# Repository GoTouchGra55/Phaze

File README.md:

# Phaze
A field-oriented control board designed to be used with a brushless motor.

## Overview
Phaze is my attempt at making a custom FOC driver. It utilizes the CAN protocol for communication between a main board and the driver, but it can also be programmed directly via an STLink-V2 debugger. 

The main goal of this project was to explore the hardware side of field-oriented control, especially the design of a dedicated motor driver and the electronics required to control a bldc motor. I wanted to design my own board and understand how all the different sections work together, rather than relying on any existing motor controllers.

## Design

SEE [SCHEMATICS](KiCAD/Phaze.pdf)

## Build Instructions
1. Order the PCB using the provided [files](KiCAD/production).
2. Solder all SMD components according to the schematic and PCB layout.
3. Inspect all solder joints and check for shorts.
4. Connect the peripherals according to the schematic.
5. Flash the firmware and verify all interfaces.
6. Test the power rails before connecting the motors.

## IMPORTANT
1. Use a 3-4s LiPo battery if you decide to use this board in your project. Discard the battery if it smells "funny".

2. Check for any damage on the pcb as it can be the reason for a catastrophic failure.

## Bill Of Materials
| # | Component / Item | Specifications | Qty. | Price (USD) | Link |
|---:|---|---|---:|---:|---:|
| 1 | SMD Resistor Assortment | 660 pcs, mixed packages and values | 1  | $0 | [Daraz](https://www.daraz.com.np/products/000000pcs-040222-10hm-910k-ohm-5-80llasex-cp0pcs-u003d-4000pcs-i416649373-s1793309546.html?c=&channelLpJumpArgs=&clickTrackInfo=query%253Asmd%252Bresistors%253Bnid%253A416649373%253Bsrc%253ALazadaMainSrp%253Brn%253Aa5197133a3019ce49e53177277acb4a7%253Bregion%253Anp%253Bsku%253A416649373_NP%253Bprice%253A1305%253Bclient%253Adesktop%253Bsupplier_id%253A900273856834%253Bsession_id%253A%253Bbiz_source%253Ahttps%253A%252F%252Fwww.daraz.com.np%252F%253Bslot%253A5%253Butlog_bucket_id%253A470687%253Basc_category_id%253A10000489%253Bitem_id%253A416649373%253Bsku_id%253A1793309546%253Bshop_id%253A191864%253BtemplateInfo%253A&freeshipping=0&fs_ab=1&fuse_fs=&lang=en&location=Overseas&price=1305&priceCompare=skuId%3A1793309546%3Bsource%3Alazada-search-voucher%3Bsn%3Aa5197133a3019ce49e53177277acb4a7%3BoriginPrice%3A130500%3BdisplayPrice%3A130500%3BisGray%3Afalse%3BsinglePromotionId%3A-1%3BsingleToolCode%3AmockedSalePrice%3BvoucherPricePlugin%3A0%3Btimestamp%3A1794537582362&ratingscore=&request_id=a5197133a3019ce49e53177277acb4a7&review=&sale=3&search=1&source=search&spm=a2a0e.searchlist.list.5&stock=1) |
| 2 | SMD Ceramic Capacitor Assortment | 2,500 pcs, 50 values, mixed packages | 1  | $0 | [Daraz](https://www.daraz.com.np/products/2500pcs-50-values-capacitor-smd-0402-0603-0805-smd-ceramic-capacitors-assortment-kit-1p-10uf-1pf-5pf-10pf-100pf-1nf-102-333-474-i1514281975-s12310158935.html?c=&channelLpJumpArgs=&clickTrackInfo=query%253Asmd%252Bcapacitor%252B0402%253Bnid%253A1514281975%253Bsrc%253ALazadaMainSrp%253Brn%253Abb4c895be7dbb09066bdbc9410dfb62b%253Bregion%253Anp%253Bsku%253A1514281975_NP%253Bprice%253A1356%253Bclient%253Adesktop%253Bsupplier_id%253A900279168309%253Bsession_id%253A%253Bbiz_source%253Ah5_external%253Bslot%253A0%253Butlog_bucket_id%253A470687%253Basc_category_id%253A10001489%253Bitem_id%253A1514281975%253Bsku_id%253A12310158935%253Bshop_id%253A198893%253BtemplateInfo%253A&configId=choice_NP_promotion&freeshipping=0&fs_ab=1&fuse_fs=&lang=en&location=Overseas&price=1356&priceCompare=skuId%3A12310158935%3Bsource%3Alazada-search-voucher%3Bsn%3Abb4c895be7dbb09066bdbc9410dfb62b%3BoriginPrice%3A135600%3BdisplayPrice%3A135600%3BisGray%3Afalse%3BsinglePromotionId%3A-1%3BsingleToolCode%3AmockedSalePrice%3BvoucherPricePlugin%3A0%3Btimestamp%3A1794537638805&ratingscore=&request_id=bb4c895be7dbb09066bdbc9410dfb62b&review=&sale=0&search=1&source=search&spm=a211g0.searchlist.list.0&stock=1&upItemIds=1514281975) |
| 3 | JLCPCB PCB Fabrication & Assembly | PCB manufacturing and assembly order | 1 order | $241.02 | [JLCPCB](https://jlcpcb.com)
| | **GRAND TOTAL** | | | **$241.02** | |

## License
### MIT License - See [LICENSE](LICENSE)

## Author
### Shaurya Tamang  
Contact: [Email](shauryatamang.dev@gmail.com)

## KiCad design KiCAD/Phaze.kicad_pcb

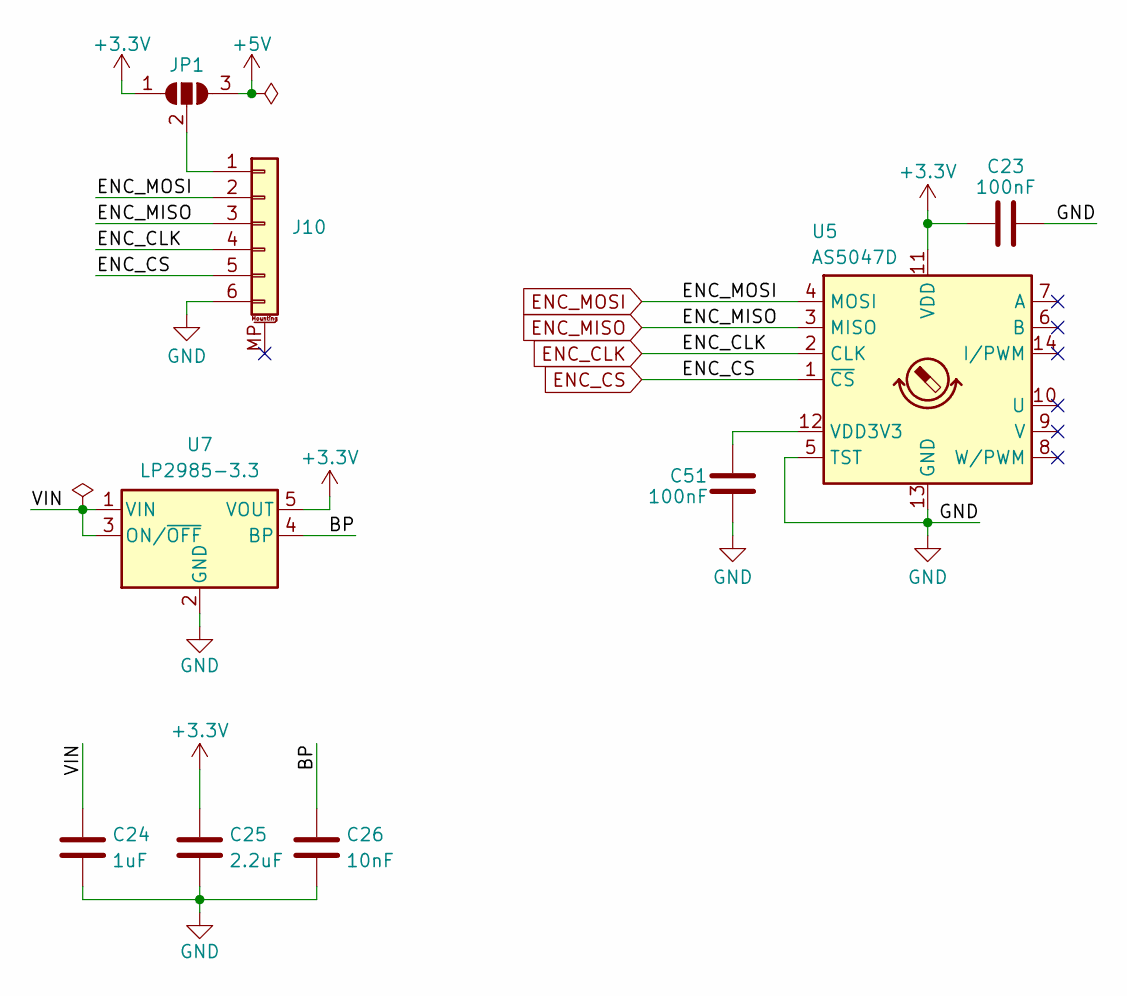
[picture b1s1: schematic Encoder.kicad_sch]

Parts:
C23, C51: 100nF; C_0402_1005Metric
C24: 1uF; C_0603_1608Metric
C25: 2.2uF; C_0603_1608Metric
C26: 10nF; C_0402_1005Metric
J10: Conn_01x06_MountingPin; JST_SH_SM06B-SRSS-TB_1x06-1MP_P1.00mm_Horizontal
JP1: SolderJumper_3_Open; SolderJumper-3_P1.3mm_Open_Pad1.0x1.5mm_NumberLabels
U5: AS5047D; TSSOP-14_4.4x5mm_P0.65mm
U7: LP2985-3.3; SOT-23-5

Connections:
+3.3V: C23.1, C25.1, JP1.1 (A), U5.11 (VDD), U7.5 (VOUT); also elsewhere on the board
+5V: JP1.3 (B); also elsewhere on the board
/Encoder/BP: C26.1, U7.4 (BP)
ENC_CLK: J10.4, U5.2 (CLK); also elsewhere on the board
ENC_CS: J10.5, U5.1 (~CS); also elsewhere on the board
ENC_MISO: J10.3, U5.3 (MISO); also elsewhere on the board
ENC_MOSI: J10.2, U5.4 (MOSI); also elsewhere on the board
GND: C23.2, C24.2, C25.2, C26.2, C51.1, J10.6, U5.5 (TST), U5.13 (GND), U7.2 (GND); also elsewhere on the board
unnamed: J10.1, JP1.2 (C)
unnamed: C51.2, U5.12 (VDD3V3)
VCC: C24.1, U7.1 (VIN), U7.3 (ON/~OFF); also elsewhere on the board

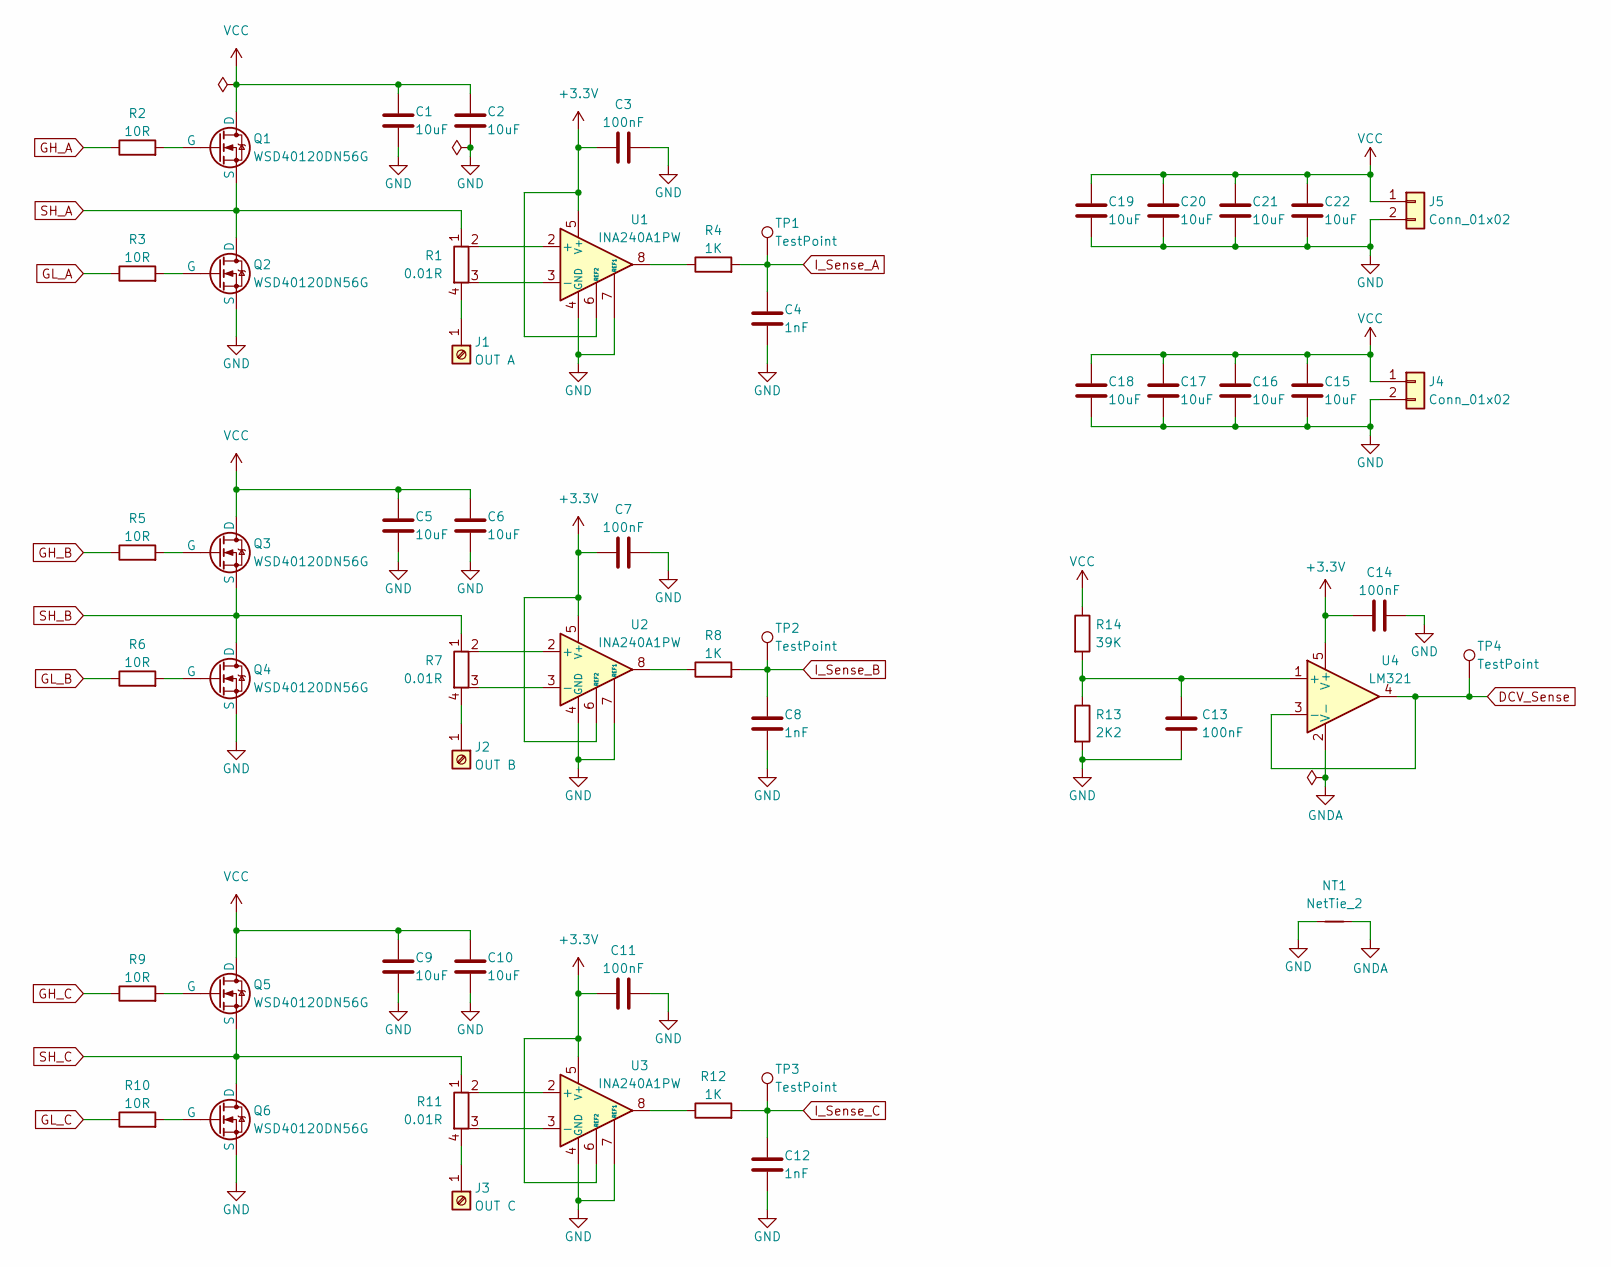
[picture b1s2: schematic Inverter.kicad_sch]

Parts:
C1, C2, C5, C6, C9, C10, C15, C16, C17, C18, C19, C20, C21, C22: 10uF; C_0603_1608Metric
C3, C7, C11, C13, C14: 100nF; C_0402_1005Metric
C4, C8, C12: 1nF; C_0402_1005Metric
J1: OUT A; CONN_01x01
J2: OUT B; CONN_01x01
J3: OUT C; CONN_01x01
J4, J5: Conn_01x02; AMASS_XT60PW-M_1x02_P7.20mm_Horizontal
NT1: NetTie_2; NetTie-2_SMD_Pad0.5mm
Q1, Q2, Q3, Q4, Q5, Q6: WSD40120DN56G; AO_DFN-8-1EP_5.55x5.2mm_P1.27mm_EP4.12x4.6mm
R1, R7, R11: 0.01R; R_Shunt_Vishay_WSK2512_6332Metric_T1.19mm
R2, R3, R5, R6, R9, R10: 10R; R_0402_1005Metric
R4, R8, R12: 1K; R_0402_1005Metric
R13: 2K2; R_0603_1608Metric
R14: 39K; R_0805_2012Metric
TP1, TP2, TP3, TP4: TestPoint; TestPoint_Pad_D1.5mm
U1, U2, U3: INA240A1PW; TSSOP-8_4.4x3mm_P0.65mm
U4: LM321; SOT-23-5

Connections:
+3.3V: C3.1, C7.1, C11.1, C14.1, U1.5 (V+), U1.6 (REF2), U2.5 (V+), U2.6 (REF2), U3.5 (V+), U3.6 (REF2), U4.5 (V+); also elsewhere on the board
DCV_Sense: TP4.1 (1_1), U4.3 (-), U4.4; also elsewhere on the board
GH_A: R2.1; also elsewhere on the board
GH_B: R5.1; also elsewhere on the board
GH_C: R9.1; also elsewhere on the board
GL_A: R3.1; also elsewhere on the board
GL_B: R6.1; also elsewhere on the board
GL_C: R10.1; also elsewhere on the board
GND: C1.2, C2.2, C3.2, C4.2, C5.2, C6.2, C7.2, C8.2, C9.2, C10.2, C11.2, C12.2, C13.2, C14.2, C15.2, C16.2, C17.2, C18.2, C19.2, C20.2, C21.2, C22.2, J4.2, J5.2, NT1.1, Q2.3 (S), Q4.3 (S), Q6.3 (S), R13.2, U1.1 (GND), U1.4 (GND), U1.7 (REF1), U2.1 (GND), U2.4 (GND), U2.7 (REF1), U3.1 (GND), U3.4 (GND), U3.7 (REF1); also elsewhere on the board
GNDA: NT1.2, U4.2 (V-)
I_Sense_A: C4.1, R4.2, TP1.1 (1_1); also elsewhere on the board
I_Sense_B: C8.1, R8.2, TP2.1 (1_1); also elsewhere on the board
I_Sense_C: C12.1, R12.2, TP3.1 (1_1); also elsewhere on the board
unnamed: J1.1 (Pin_1_1), R1.4
unnamed: J2.1 (Pin_1_1), R7.4
unnamed: J3.1 (Pin_1_1), R11.4
unnamed: Q1.2 (G), R2.2
unnamed: Q2.2 (G), R3.2
unnamed: Q3.2 (G), R5.2
unnamed: Q4.2 (G), R6.2
unnamed: Q5.2 (G), R9.2
unnamed: Q6.2 (G), R10.2
unnamed: R4.1, U1.8
unnamed: R8.1, U2.8
unnamed: R12.1, U3.8
unnamed: R1.2, U1.2 (+)
unnamed: R1.3, U1.3 (-)
unnamed: R7.2, U2.2 (+)
unnamed: R7.3, U2.3 (-)
unnamed: R11.2, U3.2 (+)
unnamed: R11.3, U3.3 (-)
unnamed: C13.1, R13.1, R14.2, U4.1 (+)
SH_A: Q1.3 (S), Q2.1 (D), R1.1; also elsewhere on the board
SH_B: Q3.3 (S), Q4.1 (D), R7.1; also elsewhere on the board
SH_C: Q5.3 (S), Q6.1 (D), R11.1; also elsewhere on the board
VCC: C1.1, C2.1, C5.1, C6.1, C9.1, C10.1, C15.1, C16.1, C17.1, C18.1, C19.1, C20.1, C21.1, C22.1, J4.1, J5.1, Q1.1 (D), Q3.1 (D), Q5.1 (D), R14.1; also elsewhere on the board

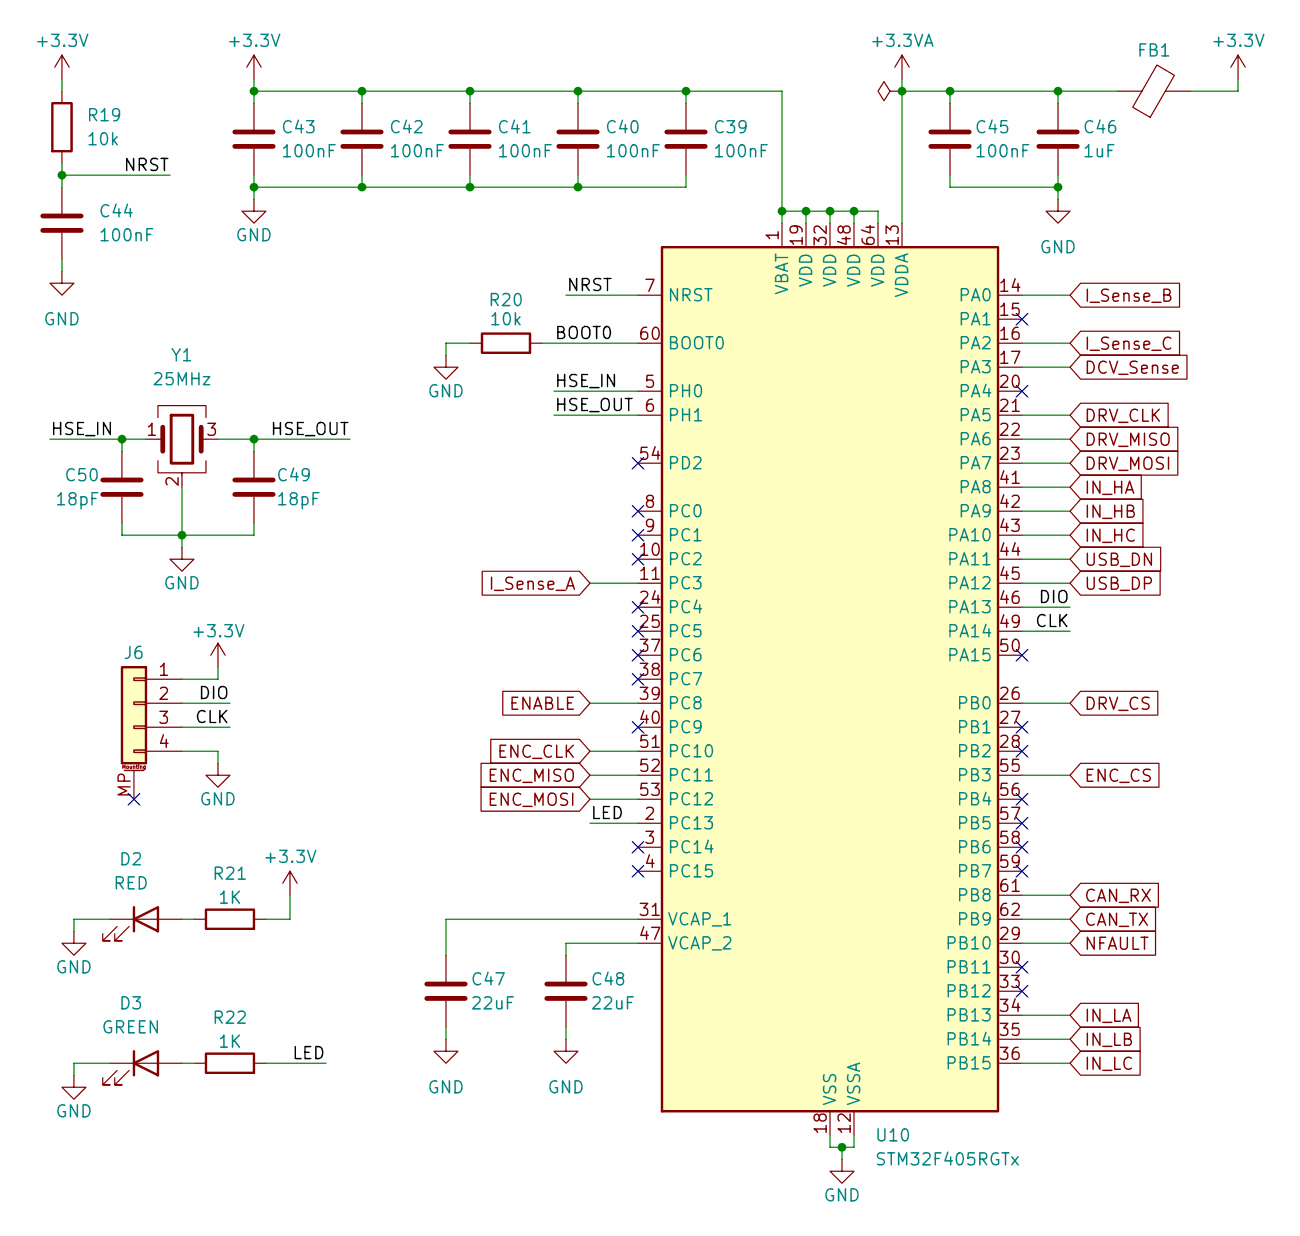
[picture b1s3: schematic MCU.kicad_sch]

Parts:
C39, C40, C41, C42, C43: 100nF; C_0402_1005Metric
C44, C45: 100nF; C_0402_1005Metric; LCSC Part # C1525
C46: 1uF; C_0603_1608Metric; LCSC Part # C29266
C47, C48: 22uF; C_0603_1608Metric; LCSC Part # C1525
C49, C50: 18pF; C_0402_1005Metric
D2: RED; LED_0402_1005Metric
D3: GREEN; LED_0402_1005Metric
FB1: fcm 1608-0603; D_0603_1608Metric; LCSC Part # C19330
J6: Conn_01x04_MountingPin; JST_SH_SM04B-SRSS-TB_1x04-1MP_P1.00mm_Horizontal
R19, R20: 10k; R_0603_1608Metric; LCSC Part # C60490
R21, R22: 1K; R_0402_1005Metric
U10: STM32F405RGTx; LQFP-64_10x10mm_P0.5mm
Y1: 25MHz; Crystal_SMD_3225-4Pin_3.2x2.5mm

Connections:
+3.3V: C39.1, C40.1, C41.1, C42.1, C43.1, FB1.2, J6.1, R19.1, R21.2, U10.1 (VBAT), U10.19 (VDD), U10.32 (VDD), U10.48 (VDD), U10.64 (VDD); also elsewhere on the board
+3.3VA: C45.1, C46.1, FB1.1, U10.13 (VDDA)
/MCU/BOOT0: R20.2, U10.60 (BOOT0)
/MCU/CLK: J6.3, U10.49 (PA14)
/MCU/DIO: J6.2, U10.46 (PA13)
/MCU/HSE_IN: C50.1, U10.5 (PH0), Y1.1
/MCU/HSE_OUT: C49.1, U10.6 (PH1), Y1.3
/MCU/LED: R22.2, U10.2 (PC13)
/MCU/NRST: C44.1, R19.2, U10.7 (NRST)
CAN_RX: U10.61 (PB8); also elsewhere on the board
CAN_TX: U10.62 (PB9); also elsewhere on the board
DCV_Sense: U10.17 (PA3); also elsewhere on the board
DRV_CLK: U10.21 (PA5); also elsewhere on the board
DRV_CS: U10.26 (PB0); also elsewhere on the board
DRV_MISO: U10.22 (PA6); also elsewhere on the board
DRV_MOSI: U10.23 (PA7); also elsewhere on the board
ENABLE: U10.39 (PC8); also elsewhere on the board
ENC_CLK: U10.51 (PC10); also elsewhere on the board
ENC_CS: U10.55 (PB3); also elsewhere on the board
ENC_MISO: U10.52 (PC11); also elsewhere on the board
ENC_MOSI: U10.53 (PC12); also elsewhere on the board
GND: C39.2, C40.2, C41.2, C42.2, C43.2, C44.2, C45.2, C46.2, C47.2, C48.2, C49.2, C50.2, D2.1 (K), D3.1 (K), J6.4, R20.1, U10.12 (VSSA), U10.18 (VSS), U10.63 (VSS), Y1.2 (G), Y1.4 (G); also elsewhere on the board
IN_HA: U10.41 (PA8); also elsewhere on the board
IN_HB: U10.42 (PA9); also elsewhere on the board
IN_HC: U10.43 (PA10); also elsewhere on the board
IN_LA: U10.34 (PB13); also elsewhere on the board
IN_LB: U10.35 (PB14); also elsewhere on the board
IN_LC: U10.36 (PB15); also elsewhere on the board
I_Sense_A: U10.11 (PC3); also elsewhere on the board
I_Sense_B: U10.14 (PA0); also elsewhere on the board
I_Sense_C: U10.16 (PA2); also elsewhere on the board
NFAULT: U10.29 (PB10); also elsewhere on the board
unnamed: D2.2 (A), R21.1
unnamed: D3.2 (A), R22.1
unnamed: C47.1, U10.31 (VCAP_1)
unnamed: C48.1, U10.47 (VCAP_2)
USB_DN: U10.44 (PA11); also elsewhere on the board
USB_DP: U10.45 (PA12); also elsewhere on the board

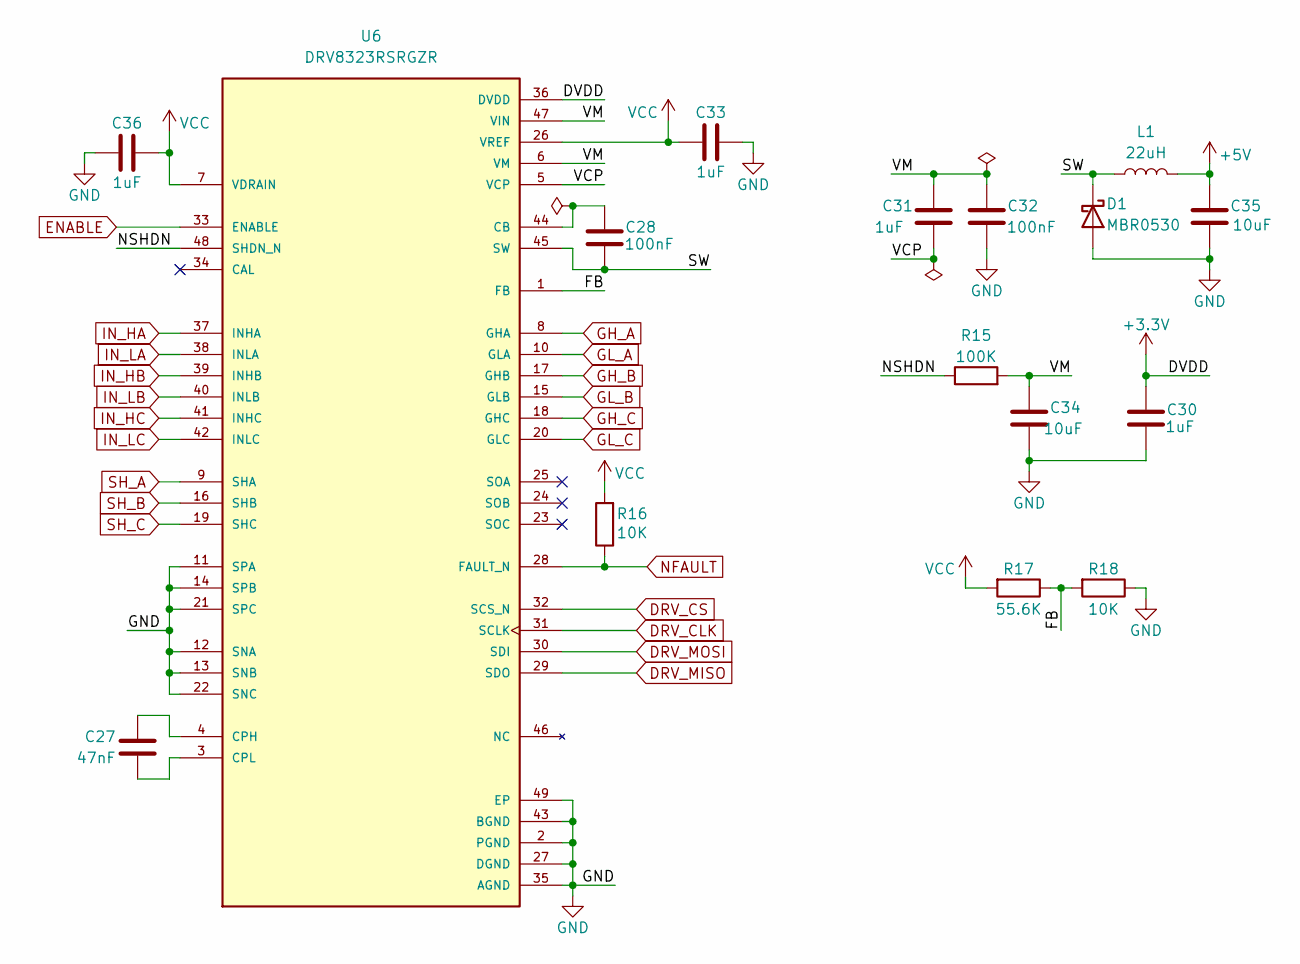
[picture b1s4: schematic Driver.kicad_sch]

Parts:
C27: 47nF; C_0402_1005Metric
C28, C32: 100nF; C_0402_1005Metric
C30, C31, C33, C36: 1uF; C_0603_1608Metric
C34, C35: 10uF; C_0603_1608Metric
D1: MBR0530; D_SOD-123; LCSC Part # C5204746
L1: 22uH; L_Cenker_CKCS3015
R15: 100K; R_0805_2012Metric
R16, R18: 10K; R_0603_1608Metric
R17: 55.6K; R_0805_2012Metric
U6: DRV8323RSRGZR; QFN50P700X700X100-49N; PARTREV C

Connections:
+3.3V: C30.1, U6.36 (DVDD); also elsewhere on the board
+5V: C35.2, L1.2; also elsewhere on the board
/Driver/FB: R17.1, R18.2, U6.1 (FB)
/Driver/NSHDN: R15.1, U6.48 (SHDN_N)
/Driver/SW: C28.1, D1.1 (K), L1.1, U6.45 (SW)
/Driver/VCP: C31.1, U6.5 (VCP)
/Driver/VM: C31.2, C32.2, C34.2, R15.2, U6.6 (VM), U6.47 (VIN)
DRV_CLK: U6.31 (SCLK); also elsewhere on the board
DRV_CS: U6.32 (SCS_N); also elsewhere on the board
DRV_MISO: U6.29 (SDO); also elsewhere on the board
DRV_MOSI: U6.30 (SDI); also elsewhere on the board
ENABLE: U6.33 (ENABLE); also elsewhere on the board
GH_A: U6.8 (GHA); also elsewhere on the board
GH_B: U6.17 (GHB); also elsewhere on the board
GH_C: U6.18 (GHC); also elsewhere on the board
GL_A: U6.10 (GLA); also elsewhere on the board
GL_B: U6.15 (GLB); also elsewhere on the board
GL_C: U6.20 (GLC); also elsewhere on the board
GND: C30.2, C32.1, C33.2, C34.1, C35.1, C36.2, D1.2 (A), R18.1, U6.2 (PGND), U6.11 (SPA), U6.12 (SNA), U6.13 (SNB), U6.14 (SPB), U6.21 (SPC), U6.22 (SNC), U6.27 (DGND), U6.35 (AGND), U6.43 (BGND), U6.49 (EP); also elsewhere on the board
IN_HA: U6.37 (INHA); also elsewhere on the board
IN_HB: U6.39 (INHB); also elsewhere on the board
IN_HC: U6.41 (INHC); also elsewhere on the board
IN_LA: U6.38 (INLA); also elsewhere on the board
IN_LB: U6.40 (INLB); also elsewhere on the board
IN_LC: U6.42 (INLC); also elsewhere on the board
NFAULT: R16.1, U6.28 (FAULT_N); also elsewhere on the board
unnamed: C28.2, U6.44 (CB)
unnamed: C27.2, U6.4 (CPH)
unnamed: C27.1, U6.3 (CPL)
SH_A: U6.9 (SHA); also elsewhere on the board
SH_B: U6.16 (SHB); also elsewhere on the board
SH_C: U6.19 (SHC); also elsewhere on the board
VCC: C33.1, C36.1, R16.2, R17.2, U6.7 (VDRAIN), U6.26 (VREF); also elsewhere on the board

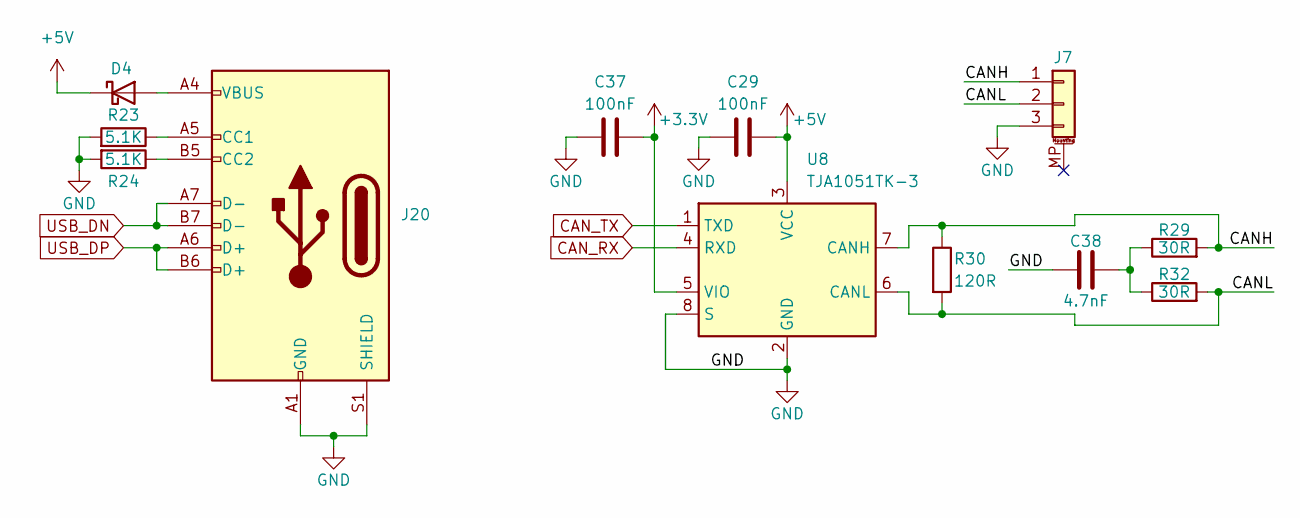
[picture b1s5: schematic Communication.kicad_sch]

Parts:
C29, C37: 100nF; C_0402_1005Metric
C38: 4.7nF; C_0402_1005Metric
D4: D_Schottky; D_SOD-123
J7: Conn_01x03_MountingPin; JST_SH_SM03B-SRSS-TB_1x03-1MP_P1.00mm_Horizontal
J20: USB_C_Receptacle_USB2.0_14P; USB_C_Receptacle_GCT_USB4105-xx-A_16P_TopMnt_Horizontal
R23, R24: 5.1K; R_0402_1005Metric
R29: 30R; R_0402_1005Metric; LCSC Part # C852718
R30: 120R; R_0402_1005Metric; LCSC Part # C125925
R32: 30R; R_0402_1005Metric_Pad0.72x0.64mm_HandSolder; LCSC Part # C852718
U8: TJA1051TK-3; HVSON-8-1EP_3x3mm_P0.65mm_EP1.6x2.4mm

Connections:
+3.3V: C37.2, U8.5 (VIO); also elsewhere on the board
+5V: C29.2, D4.1 (K), U8.3 (VCC); also elsewhere on the board
/Communication/CANH: J7.1, R29.2, R30.1, U8.7 (CANH)
/Communication/CANL: J7.2, R30.2, R32.2, U8.6 (CANL)
CAN_RX: U8.4 (RXD); also elsewhere on the board
CAN_TX: U8.1 (TXD); also elsewhere on the board
GND: C29.1, C37.1, C38.1, J7.3, J20.A1 (GND), J20.A12 (GND), J20.B1 (GND), J20.B12 (GND), J20.S1 (SHIELD), R23.2, R24.2, U8.2 (GND), U8.8 (S), U8.9 (GND); also elsewhere on the board
unnamed: C38.2, R29.1, R32.1
unnamed: D4.2 (A), J20.A4 (VBUS), J20.A9 (VBUS), J20.B4 (VBUS), J20.B9 (VBUS)
unnamed: J20.A5 (CC1), R23.1
unnamed: J20.A6 (D+), J20.B6 (D+)
unnamed: J20.A7 (D-), J20.B7 (D-)
unnamed: J20.B5 (CC2), R24.1

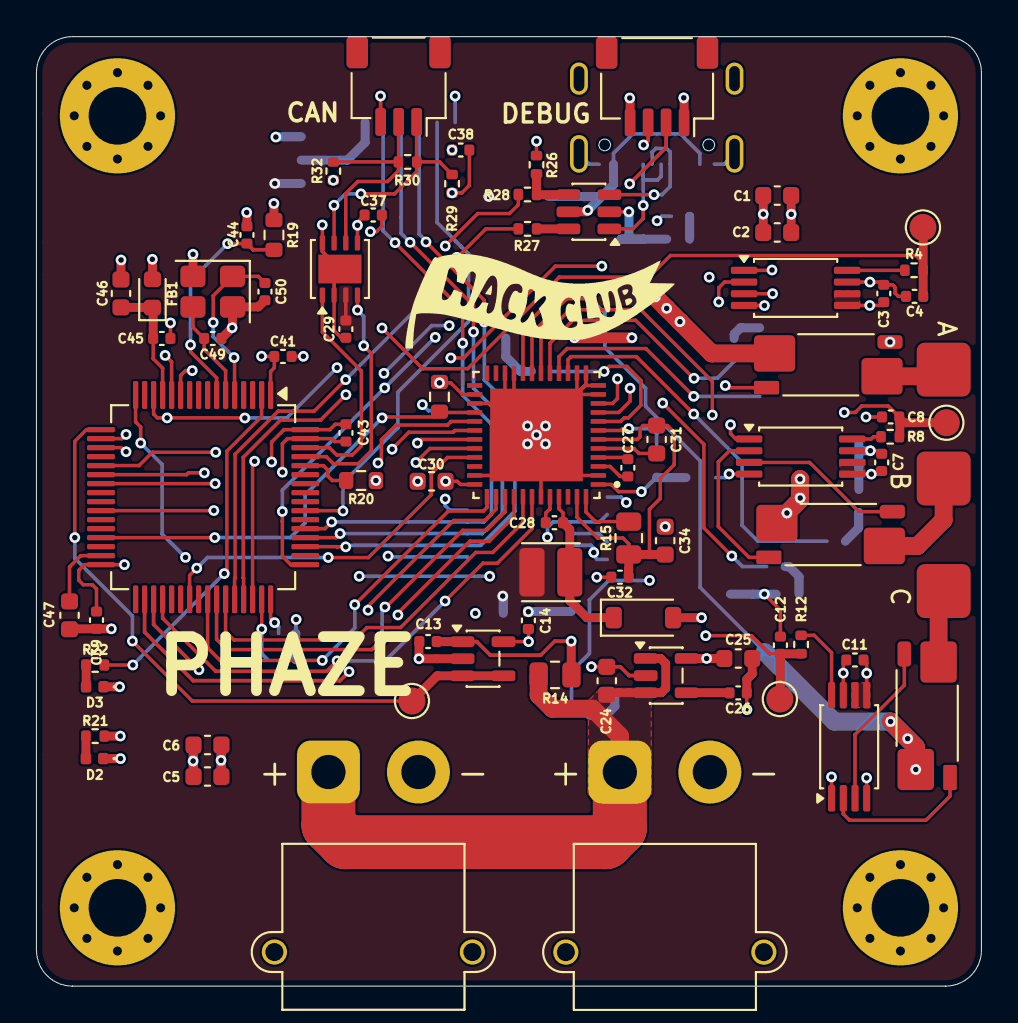
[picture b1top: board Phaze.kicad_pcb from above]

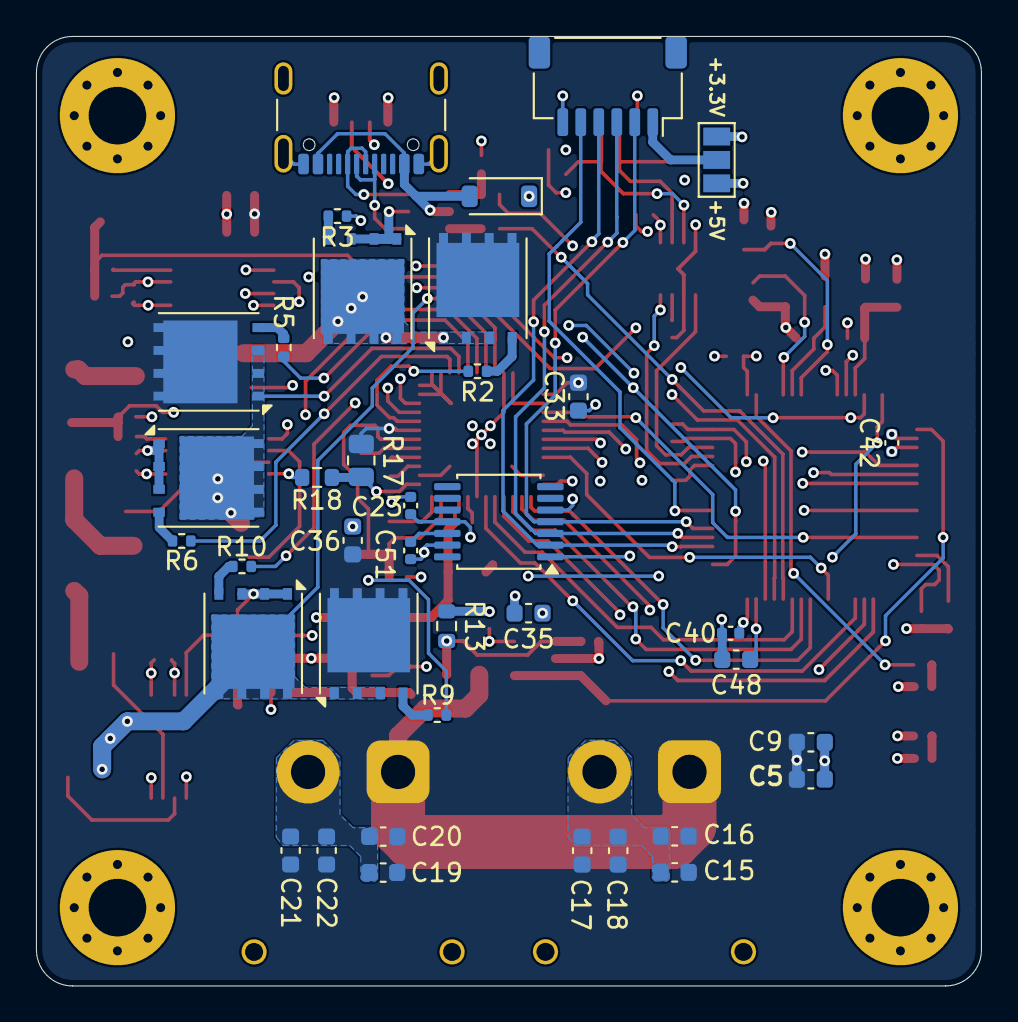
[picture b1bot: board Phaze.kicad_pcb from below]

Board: 4 copper layers, 52.5 x 52.8 mm, 117 parts (38 on the bottom side), 88 nets.

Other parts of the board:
D5: MBR0530; D_SOD-123
J8: USB_C_Receptacle_USB2.0_16P; USB_C_Receptacle_GCT_USB4105-xx-A_16P_TopMnt_Horizontal
R26: 1k8; R_0402_1005Metric
R27, R28: 100R; R_0402_1005Metric
U9: USBLC6-2SC6; SOT-23-6

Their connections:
+3.3V: R26.1; also elsewhere on the board
+5V: D5.1 (K); also elsewhere on the board
GND: J8.A1 (GND), J8.A12 (GND), J8.B1 (GND), J8.B12 (GND), J8.SH (SHIELD), U9.2 (GND); also elsewhere on the board
unnamed: D5.2 (A), J8.A4 (VBUS), J8.A9 (VBUS), J8.B4 (VBUS), J8.B9 (VBUS), U9.5 (VBUS)
unnamed: J8.A6 (D+), J8.B6 (D+), U9.3 (I/O2)
unnamed: J8.A7 (D-), J8.B7 (D-), U9.1 (I/O1)
unnamed: R26.2, R28.1, U9.4 (I/O2)
unnamed: R27.1, U9.6 (I/O1)
USB_DN: R27.2; also elsewhere on the board
USB_DP: R28.2; also elsewhere on the board

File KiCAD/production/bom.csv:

Designator,Footprint,Quantity,Value,LCSC Part #
"C1, C10, C15, C16, C17, C18, C19, C2, C20, C21, C22, C34, C35, C5, C6, C9",0603,16,10uF,
"C11, C13, C14, C23, C28, C29, C3, C32, C37, C39, C40, C41, C42, C43, C51, C7",0402,16,100nF,
"C12, C4, C8",0402,3,1nF,
"C24, C30, C31, C33, C36",0603,5,1uF,
C25,0603,1,2.2uF,
C26,0402,1,10nF,
C27,0402,1,47nF,
C38,0402,1,4.7nF,
"C44, C45",0402,2,100nF,C1525
C46,0603,1,1uF,C29266
"C47, C48",0603,2,22uF,C1525
"C49, C50",0402,2,18pF,
"D1, D5",D_SOD-123,2,MBR0530,C5204746
D2,0402,1,RED,
D3,0402,1,GREEN,
FB1,0603,1,fcm 1608-0603,C19330
J1,CONN_01x01,1,OUT A,
J10,JST_SH_SM06B-SRSS-TB_1x06-1MP_P1.00mm_Horizontal,1,Conn_01x06_MountingPin,
J2,CONN_01x01,1,OUT B,
J3,CONN_01x01,1,OUT C,
"J4, J5",AMASS_XT30PW-M_1x02_P2.50mm_Horizontal,2,Conn_01x02,
J6,JST_SH_SM04B-SRSS-TB_1x04-1MP_P1.00mm_Horizontal,1,Conn_01x04_MountingPin,
J7,JST_SH_SM03B-SRSS-TB_1x03-1MP_P1.00mm_Horizontal,1,Conn_01x03_MountingPin,
J8,USB_C_Receptacle_GCT_USB4105-xx-A_16P_TopMnt_Horizontal,1,USB_C_Receptacle_USB2.0_16P,
L1,L_Cenker_CKCS3015,1,22uH,
"Q1, Q2, Q3, Q4, Q5, Q6",AO_DFN-8-1EP_5.55x5.2mm_P1.27mm_EP4.12x4.6mm,6,WSD40120DN56G,
"R1, R11, R7",R_Shunt_Vishay_WSK2512_6332Metric_T1.19mm,3,0.01R,
"R10, R2, R3, R5, R6, R9",0402,6,10R,
"R12, R21, R22, R4, R8",0402,5,1K,
R13,0603,1,2K2,
R14,0805,1,39K,
R15,0805,1,100K,
"R16, R18",0603,2,10K,
R17,0805,1,55.6K,
"R19, R20",0603,2,10k,C60490
R26,0402,1,1k8,C163481
"R27, R28",0402,2,100R,C705627
"R29, R32",0402,2,30R,C852718
R30,0402,1,120R,C125925
"TP1, TP2, TP3, TP4",TestPoint_Pad_D1.5mm,4,TestPoint,
"U1, U2, U3",TSSOP-8_4.4x3mm_P0.65mm,3,INA240A1PW,
U10,LQFP-64_10x10mm_P0.5mm,1,STM32F405RGTx,
U4,SOT-23-5,1,LM321,
U5,TSSOP-14_4.4x5mm_P0.65mm,1,AS5047D,
U6,QFN50P700X700X100-49N,1,DRV8323RSRGZR,
U7,SOT-23-5,1,LP2985-3.3,
U8,HVSON-8-1EP_3x3mm_P0.65mm_EP1.6x2.4mm,1,TJA1051TK-3,
U9,SOT-23-6,1,USBLC6-2SC6,C2827654
Y1,Crystal_SMD_3225-4Pin_3.2x2.5mm,1,25MHz,
